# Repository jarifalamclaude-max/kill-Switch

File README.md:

# Magnetic Kill Switch (100 A)

Magnetic kill switch for an underwater robot on a 4S–6S LiPo. The board sits inside the hull and the magnet plug sits outside. Plug in: the ESCs get power. Pull the plug out: power is cut about 1.5 ms later.

There are two boards with the **same circuit**, both for **100 A** with **XT90 in (battery) and XT90 out (ESCs)**:

| | Through-hole | SMD (small) |
|---|---|---|
| Board | `kicad/ks_tht.kicad_pcb`, 123 × 100 mm | `kicad/ks_smd.kicad_pcb`, 80 × 75 mm |
| Parts | 108 (4 of them test pads), all through-hole | 96 (4 of them test pads): TOLL, SOIC, SOT-23, 0805; XT90s, B0512S and sensor plugs through-hole |
| Switch | 8 × IRFB3206 (TO-220) | 4 × IPT007N06N (TOLL) |
| Controller | one LM339 + isolated gate supply (B0512S) + PC817 | same circuit in SMD parts |
| 100 A path | bare copper strips with 8 AWG bare wire soldered on | same idea |
| Copper | 2 layers, 2 oz, green solder mask | same |

**Neither board has been built or tested yet.** Everything below comes from calculations, KiCad DRC (0 violations, 0 unconnected on both boards) and ngspice simulations of the netlists taken from the PCBs: [`SIMULATION_RESULT.md`](SIMULATION_RESULT.md).

Schematic (drawn from the PCB netlist): [`docs/kill_switch_tht_schematic.png`](docs/kill_switch_tht_schematic.png), [SVG](docs/kill_switch_tht_schematic.svg).

## Opening in KiCad (3D view)

Open `kicad/ks_tht.kicad_pro` (or `ks_smd.kicad_pro`) in **KiCad 7, 8, 9 or 10**. Every 3D model the boards use is in `kicad/3dmodels/` and the footprints point at it through `${KIPRJMOD}`. The 3D view shows all parts on any of those versions, even without KiCad's 3D library installed. Keep the `kicad/` folder together (the zips do). The XT90 footprints are in the project library `kicad/ks.pretty`. KiCad 6 cannot open KiCad 7 files.

## Why no reed switch in the power path

A reed switch carries well under 1 A and burns at the arc of a DC break at tens of amps. So the magnet only drives sensors. The current is switched by MOSFETs.

## How it works

1. **Two sensors in series.** A Hall module (KY-003, A3144) and a reed door contact (MC-38) must both see the magnet before anything turns on. A Hall stuck on, a welded reed, a cut cable, a Hall without power or a shorted Hall wire still kill (all simulated).
2. **Arm delay and debounce.** The sensors pull ARM high. ARM charges EN through 100 kΩ / 10 µF, so the switch starts about 0.8 s after the plug goes in. Losing ARM empties EN through a 2N3904 in about 1.5 ms. A sensor gap shorter than about 1 ms (vibration) is ignored, and a real pull kills in about 1.5 ms.
3. **Pre-charge first.** An IRF9540N charges the ESC capacitors through a 0.5 A PTC and 2 × 22 Ω (1.4 A at 4S, 2.1 A at 6S). Without it a few hundred amps would rush into cold capacitors.
4. **One LM339 does the sequencing.**
   - EN above 2.5 V starts the pre-charge.
   - If VOUT does not keep up with a ramp that rises with VIN (a shorted ESC bus), the pre-charge stops and stays off until the magnet is pulled.
   - The main MOSFETs close only when VOUT is above half of VIN.
   - The same comparator trips when a short pulls VOUT down while running.
5. **Main switch.** 8 × IRFB3206 in parallel (through-hole board) as a high-side switch.
   - The gate supply is an isolated 5 V → 12 V module (B0512S) whose output floats on the MOSFET sources, so the gates get about 12.8 V on any pack.
   - A PC817 connects it to the gates through a diode and 10 kΩ. A 220 nF capacitor (with 100 Ω) makes VOUT ramp up gently: 19 A peak when the MOSFETs close.
   - When the opto lets go, a BC327 pulls the gates down fast (R37 = 47 kΩ lets it pull them all the way below 1.5 V).
6. **Clamps.** 1.5KE33A TVS on the battery and ESC sides, P6KE18A between gate and source, 15 V zener on the gate supply.
7. **LEDs.** Blue HALL and blue REED (each sensor sees the magnet) and red LIVE (ESCs powered).

Not included (to keep it simple): under- and over-voltage lockout, a second independent kill path, an over-current trip below a hard short, and a status line to the Jetson. **Put a 125–150 A fuse (ANL / MIDI / MEGA) in the battery + lead.** The board kills a hard short in about 0.5 ms; an overload below that is the fuse's job.

## Numbers (through-hole board, simulated)

| | Value |
|---|---|
| MOSFET drop, 8 in parallel | 25 mV at 60 A, 42 mV at 100 A |
| Board copper at 100 A, with the 8 AWG wires | 2.5 W (without the wires: 9.3 W) |
| MOSFETs at 100 A, with the wires | 4.2 W in total (25 °C max Rds(on)), 11–15 A each |
| Gate voltage | 12.8 V on 4S and 6S |
| Kill time after the magnet leaves | 1.5 ms (4S and 6S), also with any one sensor fault; 14 mJ in the MOSFETs |
| Ignored sensor gap | 0.8 ms tested (vibration) |
| Short on the ESC side while live | off in 0.43 / 0.44 ms (4S / 6S); 1.0 J / 2.3 J shared by the 8 MOSFETs; gate peak 15.7 / 16.0 V; battery side peak 26.6 / 36.3 V |
| Magnet in with the ESC side shorted | never turns on; 0.29 J in the pre-charge resistors |
| Battery spike when killing 100 A | 19.5 V peak on 4S, 27.9 V on 6S |
| SMD board (4 × IPT007N06N) | 18 mV at 100 A, gate 13.3 V, kill 1.6 ms, short off in 0.45 / 0.48 ms; with the 8 AWG wires: copper 1.8 W, MOSFETs 22–29 A each (without: 8.3 W, Q1 47 A) |

All 15 scenarios for each board, the weakest optocoupler, and the copper current solve: [`SIMULATION_RESULT.md`](SIMULATION_RESULT.md). Magnet field, sensor placement and plug retention: [`calc/report.md`](calc/report.md).

## 100 A: the bare strips and 8 AWG wire

PCB copper alone cannot carry 100 A: the 2 oz copper would lose 9 W, and the MOSFET nearest the XT90s would take 29 A of the 100. So every 100 A path has a **bare copper strip** (no solder mask). Solder **8 AWG bare copper wire** (3.3 mm solid, or bare earthing wire) along each strip:

- **VOUT** (top, above the MOSFET pins): from the J2 + pin along the whole strip.
- **VIN** (top, below the MOSFETs, under their tabs): from the J1 + pin along the whole strip.
- **GND** (bottom): bend the wire into a C on the bare strip, from the J2 − pin to the J1 − pin.

With the wires the copper loses 2.5 W at 100 A and the 8 MOSFETs share the current within 11–15 A each. The SMD board needs the same wires (VIN above the MOSFETs, VOUT below them and down to J2 +, GND underneath between the XT90 minus pins): with them its 4 MOSFETs carry 22–29 A each, without them Q1 takes 47 A. The through-hole MOSFET tabs are all VIN. A flat copper or aluminium bar bolted across all 8 tabs (M3, no insulators needed) is optional; it spreads the heat so that Q1 runs as cool as the others.

## XT90

- J1 = **XT90PW-M** (male, right-angle PCB) for the battery's XT90; J2 = **XT90PW-F** (female) for the ESC harness. Both face out of the left edge.
- An XT90 is rated **45 A continuous, 90 A burst**. Short 100 A bursts (all thrusters at full throttle for seconds) are normal XT90 use; 100 A for minutes heats each XT90 by several watts. For long 100 A runs use two XT90s per side, or AS150 / XT150 (different footprint).
- Use 8 AWG silicone cable from the battery and to the ESCs, as short as possible.

## Buying

Full lists with quantities: [`kicad/bom_tht_grouped.csv`](kicad/bom_tht_grouped.csv) (through-hole) and [`kicad/bom_smd_grouped.csv`](kicad/bom_smd_grouped.csv) (SMD). Main parts of the through-hole board:

- 8 × IRFB3206PbF (TO-220), 1 × IRF9540NPbF.
- AMASS XT90PW-M and XT90PW-F (right-angle PCB mount).
- Mornsun B0512S-1WR3 (5 V → 12 V isolated, SIP-4). Check its pin order against the board: 1 GND, 2 Vin, 3 0 V, 4 +Vo.
- LM339N (DIP-14), PC817 (DIP-4), L7805CV. A K7805-500R3 or R-78E5.0-0.5 switching module fits the 7805's holes and runs cooler on 6S.
- 2 × 1.5KE33A, P6KE18A, 1N4744A, 1N4007, 2 × 1N4148, BZX55C12.
- Littelfuse RXEF050 PTC, 2 × 22 Ω 2 W.
- About 0.35 m of 8 AWG bare copper wire, and a 125–150 A fuse for the battery lead.
- KY-003 Hall module. Check its pin order (S, +, −) with a multimeter: some clones swap + and −.
- MC-38 wired door contact, sold in Bangladesh ([ElectronicsBD](https://electronics.com.bd/components-price-in-Bangladesh/mc-38-wired-door-window-sensor-magnetic-switch-home-alarm-system), [BDTronics](https://www.bdtronics.com/mc38-magnetic-switch.html)). Listings disagree on "normally open" and "normally closed", so check with a multimeter: it must close when the magnet is near.
- N52 magnet, 15 mm diameter × 10 mm, axially magnetised.

**Ordering the PCB (JLCPCB):** upload `kill_switch_tht_gerber_jlcpcb.zip` (or `kill_switch_smd_gerber_jlcpcb.zip`). Set 2 layers, 1.6 mm, **2 oz outer copper**, green solder mask (the default), HASL.

## Wiring

- Battery → 125–150 A fuse → J1 (XT90, battery). ESC harness → J2 (XT90, ESCs). The ground passes through the board from J2 − to J1 − along the bottom GND wire.
- J3 → KY-003 (1 = S, 2 = +, 3 = −). J4 → MC-38 (2 wires, either way round).
- Run the battery + and − as a twisted pair, at least 10 cm from the sensors.
- There is no reverse-polarity protection on the power path. The XT90 is keyed, so keep it that way.

## Mechanics (side mount)

- The dock is glued to the outside of the hull (no holes through the hull). The hull wall must be non-magnetic: acrylic, polycarbonate or aluminium, not steel.
- The plug carries the magnet with its **south pole toward the hull**: the A3144 only reacts to a south pole on its printed face. If the HALL LED stays off with the plug in, flip the magnet.
- An O-ring on the plug snaps into a groove in the dock. Pulling it out takes 10–20 N, against 0.29 N of plug weight, 1.4 N at 5 g of vibration and 1.2 N of water drag at 1.5 m/s. A slot along the dock bore lets water in and out, so there is no suction and no trapped water.
- Inside, a printed bracket holds the A3144 flat against the wall on the plug's axis (9.5 mm from the magnet, about 104 mT, 3× margin) and the MC-38 12 mm off the axis. How to fit it, step by step: [`mount/`](mount/) (video with voice-over).
- Keep steel away from the sensors. Park the pulled plug at least 120 mm away (30 cm is better), never on a steel part.

## Pre-dive check

1. Plug out, battery in: all three LEDs off.
2. Push the plug in: both blue LEDs (HALL, REED) on, then about 1 s later the red LIVE LED on. If only one blue LED lights, do not dive.
3. Pull the plug: LIVE off at once, the thrusters stop.
4. Pull the plug with a luggage scale once: it should need 10–20 N.

## Check before trusting it

- Build one board and test it on a bench supply with a current limit first, then with the battery and one ESC, then at full current. After a long full-throttle run, feel the MOSFETs, the wires and the XT90s.
- Measure the KY-003 and MC-38 with the magnet: KY-003 modules use A3144 or clones, and reed sensitivity varies by maker.
- The B0512S output is unregulated (about 14 V at light load in the model); the 15 V zener and the P6KE18A keep the gate below 20 V.
- The simulation models (MOSFETs fitted to datasheet numbers, behavioural comparators, opto, isolated module) are approximations.

## Folders

| Folder / file | Contents |
|---|---|
| `kicad/build_tht.py`, `route_tht.py` | Through-hole board: parts, netlist and placement; routing (0/45-degree corners), pours, bare strips, BRACU Duburi logo and name, DRC |
| `kicad/build_smd.py`, `route_smd.py` | SMD board, same circuit |
| `kicad/ks_tht.*`, `ks_smd.*`, `drc_*.rpt`, `bom_*.csv` | KiCad boards, DRC reports, BOMs and order lists |
| `kicad/3dmodels/`, `ks.pretty/`, `fp-lib-table` | 3D models of every part (found through `${KIPRJMOD}`), XT90 footprints |
| `kicad/bundle_3d.py`, `make_xt90.py`, `make_outputs.py`, `gridroute.py` | 3D-model bundling and green stackup, XT90 footprints and models, gerbers/zips/pictures, the router |
| `kicad/simulation/` | `run_tht.py --board tht/smd` (15 scenarios from the PCB netlist), `copper_tht.py` (copper current solve), `make_result.py` |
| `gerber_tht/`, `gerber_smd/`, `kill_switch_*_gerber_jlcpcb.zip`, `kill_switch_*_kicad.zip` | Gerbers for JLCPCB and the KiCad projects (with 3D models) |
| `veroboard/` | Perfboard version of the through-hole board, with schematic, wire list and parts |
| `pcb-3d/` | 3D through-hole board with every part and the current paths on the real copper |
| `3d/` | Tutorial: video `kill_switch_tutorial.mp4` (86 s, English voice-over, 100 A board) and an interactive 3D scene of a diver pulling and re-arming the plug; `make_voice.py` + `narration/` make the voice, `render_video.js` renders and mixes it |
| `mech/` | Dock, plug, T-handle and inside sensor bracket (OpenSCAD, STL) |
| `mount/` | Sensor mounting guide: video `sensor_mounting.mp4` (72 s, English voice-over) and a 3D scene of where the Hall (KY-003) and reed (MC-38) go inside the hull and how to fit them |
| `kicad/build_ks.py`, `route_ks.py`, `ks_power.*`, `gerber/`, `kill_switch_gerber_jlcpcb.zip`, `kill_switch_kicad.zip` | First SMD version (LM5060, M5 lugs, 118 × 120 mm), kept for reference |
| `calc/` | `design_calc.py`: magnet field, reed placement, cable stray field, timing, plug retention (`report.md`) |

## Rebuilding

With KiCad 7 and its Python (`KICAD7_FOOTPRINT_DIR` and `KICAD7_SYMBOL_DIR` set to the KiCad libraries):

```bash
cd kicad && python3 build_tht.py && python3 route_tht.py && python3 make_bom.py bom_tht.csv bom_tht_grouped.csv && python3 make_outputs.py tht
```

```bash
cd kicad/simulation && python3 run_tht.py --board tht && python3 summary_tht.py --board tht && python3 copper_tht.py --board tht --wires && python3 make_result.py
```

The SMD board is the same with `build_smd.py`, `route_smd.py`, `make_outputs.py smd` and `--board smd`.

## Bangla-English summary

- Duita board, ekoi circuit, duitai 100 A: through-hole (8 ta IRFB3206, 123 × 100 mm) ar choto SMD (4 ta IPT007N06N, 80 × 75 mm).
- Battery ar ESC dui dikei XT90. XT90 45 A continuous / 90 A burst rated: thruster-er short burst thik ache; onek khon 100 A cholle 2 ta XT90 parallel ba AS150 din.
- 100 A-er jonno bare strip gulote 8 AWG khali tama-r tar solder korte hobe (VIN, VOUT upore; GND niche C shape). Tar chara copper-e 9 W gorom hoy, tar dile 2.5 W.
- Hall (KY-003) ar reed (MC-38) dutoi magnet dekhle tobei chalu hoy. Magnet tanle ~1.5 ms-e power off; chalu obosthay short hole 0.4 ms-e off; short thakle chalu-i hoy na.
- KiCad 7, 8, 9, 10 — jekono version-e khulle 3D view-te sob part dekha jabe (3D model project-er bhitorei ache). Board green.
- Battery + tare 125–150 A fuse rakho. Board ekhono banano/test kora hoyni: prothome bench supply-te current limit diye test korben.

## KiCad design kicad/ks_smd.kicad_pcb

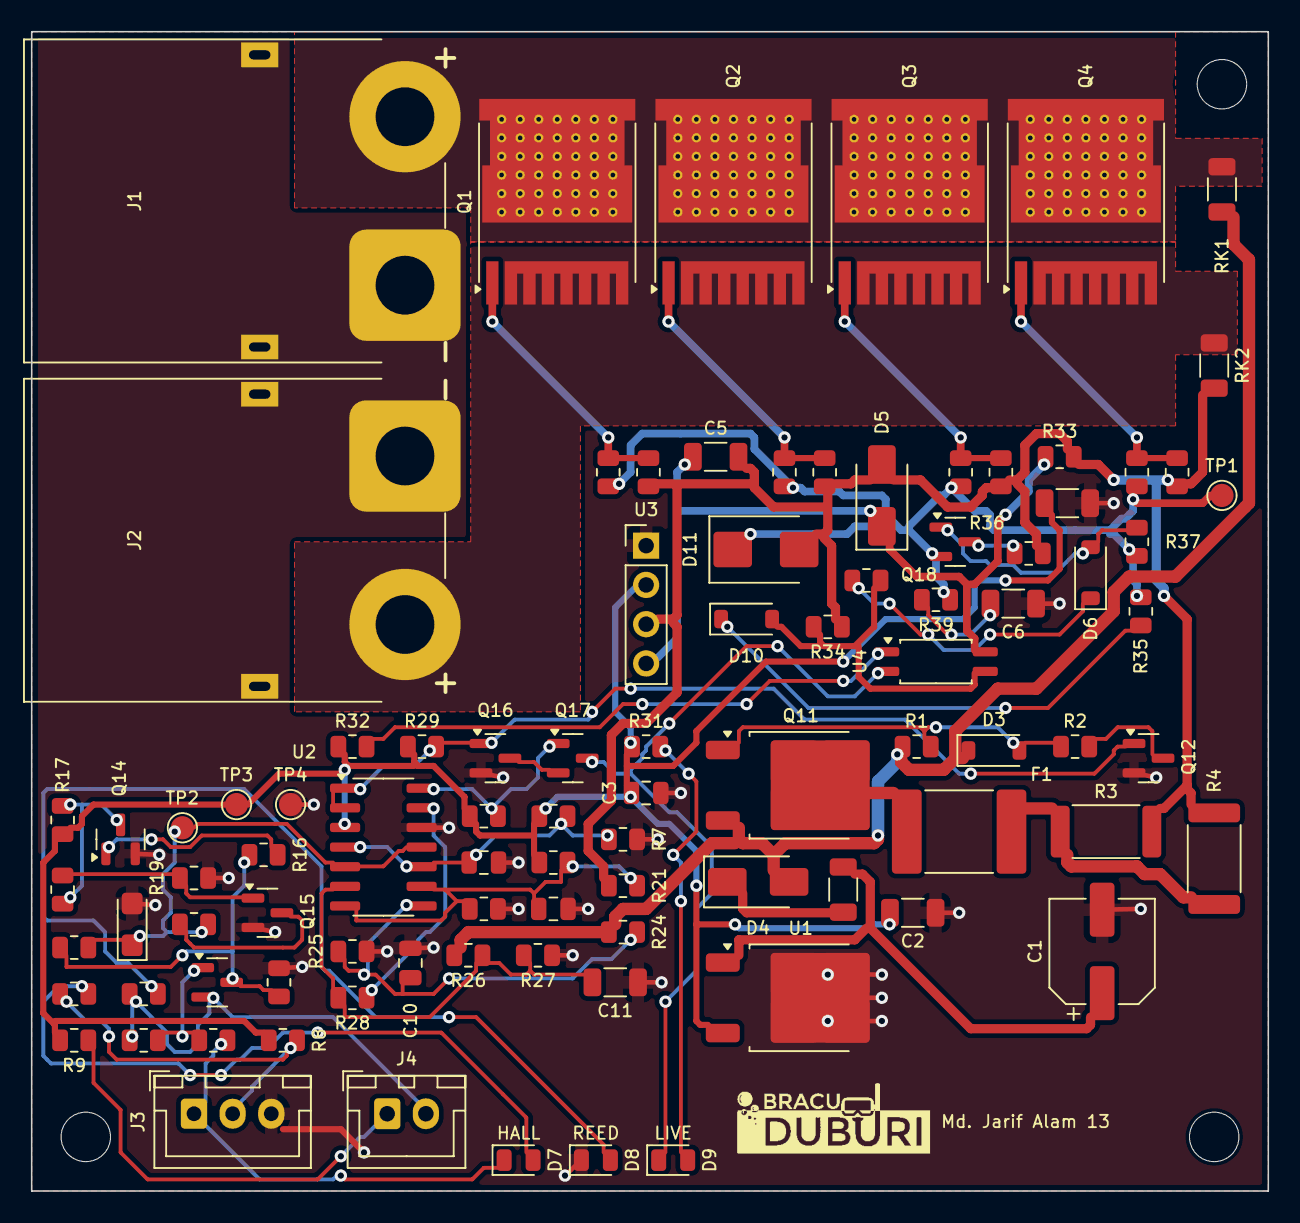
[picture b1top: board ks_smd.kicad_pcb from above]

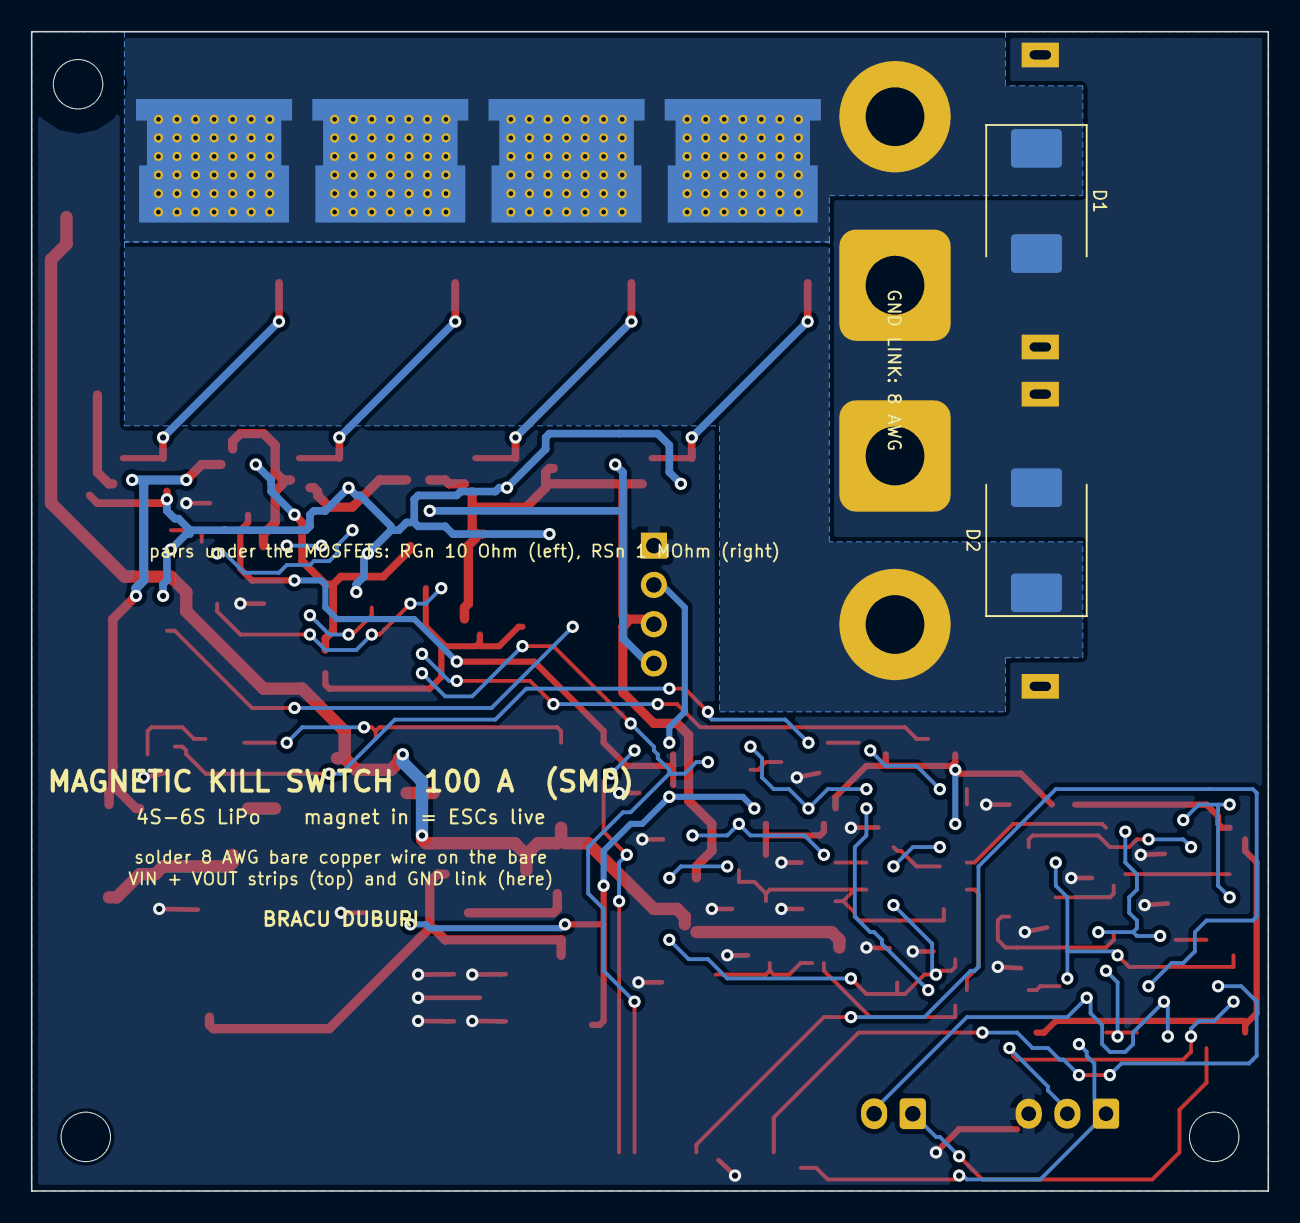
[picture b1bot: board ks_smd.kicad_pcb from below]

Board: 2 copper layers, 80.0 x 75.0 mm, 99 parts (2 on the bottom side), 48 nets.

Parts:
C1: 47u 50V; CP_Elec_6.3x7.7
C2, C4: 10u 25V; C_1206_3216Metric
C3, C8: 100n; C_0805_2012Metric
C5: 22u 25V; C_1206_3216Metric
C6: 220n 100V X7R; C_1206_3216Metric
C7: 10u 16V tantalum; CP_EIA-3216-18_Kemet-A
C9, C10: 10n; C_0805_2012Metric
C11: 3.3u X7R 50V; C_1206_3216Metric
D1, D2: SMCJ28A; D_SMC
D3: BZT52C12; D_SOD-123
D4: S1M; D_SMA
D5: SMAZ15; D_SMA
D6, D10: 1N4148W; D_SOD-123
D7: blue HALL; LED_0805_2012Metric
D8: blue REED; LED_0805_2012Metric
D9: red LIVE; LED_0805_2012Metric
D11: SMBJ15A; D_SMB
F1: MF-SM050/60-2 (0.5 A, 60 V); Fuse_2920_7451Metric
H1, H2, H3: M3 nylon; MountingHole_3.2mm_M3
J1: XT90PW-M battery IN; AMASS_XT90PW-M_1x02_P10.90mm_Horizontal
J2: XT90PW-F ESC OUT; AMASS_XT90PW-F_1x02_P10.90mm_Horizontal
J3: HALL MODULE (KY-003: S + -); JST_XH_B3B-XH-A_1x03_P2.50mm_Vertical
J4: REED (MC-38); JST_XH_B2B-XH-A_1x02_P2.50mm_Vertical
Q1, Q2, Q3, Q4: IPT007N06N; Infineon_PG-HSOF-8-1_ThermalVias
Q11: FQD11P06; TO-252-2
Q12, Q16, Q17: 2N7002; SOT-23
Q13: MMBT3906; SOT-23
Q14, Q15: MMBT3904; SOT-23
Q18: BC807-40; SOT-23
R1, R11, R37: 47k; R_0805_2012Metric
R2, R34: 22k; R_0805_2012Metric
R3, R4: 22 2512; R_2512_6332Metric
R5: 10; R_1206_3216Metric
R6, R7, R10, R16, R17, R18, R29, R30, R35: 10k; R_0805_2012Metric
R8, R9, R39: 100; R_0805_2012Metric
R12, R33: 4.7k; R_0805_2012Metric
R13, R14, R28, R31, R38: 1k; R_0805_2012Metric
R15, R19: 100k; R_0805_2012Metric
R20: 220; R_0805_2012Metric
R21: 75k 1%; R_0805_2012Metric
R22, R25: 10k 1%; R_0805_2012Metric
R23: 470k; R_0805_2012Metric
R24: 160k 1%; R_0805_2012Metric
R26: 1M; R_0805_2012Metric
R27: 68k; R_0805_2012Metric
R32: 330; R_0805_2012Metric
R36: 47; R_0805_2012Metric
RG1, RG2, RG3, RG4: 10; R_0805_2012Metric
RK1, RK2: 0R; R_1206_3216Metric
RS1, RS2, RS3, RS4: 1M; R_0805_2012Metric
TP1: FG; TestPoint_Pad_D1.5mm
TP2: EN; TestPoint_Pad_D1.5mm
TP3: V5; TestPoint_Pad_D1.5mm
TP4: GND; TestPoint_Pad_D1.5mm
U1: L7805CDT; TO-252-2
U2: LM339D; SOIC-14_3.9x8.7mm_P1.27mm
U3: B0512S-1WR3; PinHeader_1x04_P2.54mm_Vertical
U4: EL357N; SOP-4_4.4x2.6mm_P1.27mm

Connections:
ARM: Q13.3, R12.1, R15.1, R16.1
CATH: D9.1, Q17.3, U4.2
DONE: Q17.1, R30.2, U2.14
DRV: D10.2, R34.1, R38.2, U4.3
DRVD: D10.1, R35.1
EN: C7.1, R15.2, R20.2, TP2.1, U2.5, U2.11
FG: D11.1, Q18.2, R35.2, R37.1, R39.2, RG1.2, RG2.2, RG3.2, RG4.2, TP1.1
FGC: C6.1, R39.1
G1: Q1.1, RG1.1, RS1.1
G2: Q2.1, RG2.1, RS2.1
G3: Q3.1, RG3.1, RS3.1
G4: Q4.1, RG4.1, RS4.1
GND: C1.2, C2.2, C3.2, C4.2, C6.2, C7.2, C8.2, C9.2, C10.2, C11.2, D1.2, D2.2, D8.1, J1.1, J1.MP, J2.1, J2.MP, J3.3, Q12.2, Q14.2, Q15.2, Q16.2, R7.2, R12.2, R19.2, R22.2, R25.2, R27.2, TP4.1, U1.2, U2.12, U3.1
HALL: D7.1, J3.1, R10.2
HLA: D7.2, R13.2
LVA: D9.2, R31.2
NARM: Q14.3, R17.2, R18.1
PCD: F1.1, Q11.2
PCDN: Q12.3, R2.2
PCEN: Q12.1, Q16.1, R29.2, U2.1, U2.2
PCF: F1.2, R3.1, R4.1
PCG: D3.2, Q11.1, R1.2, R2.1
QAB: Q13.1, R10.1, R11.2
QDB: Q15.1, R18.2, R19.1
QDC: Q15.3, R20.1
QGM: Q16.3, Q17.2
QIB: Q14.1, R16.2
QOB: D6.2, Q18.1, R37.2
QOC: Q18.3, R36.1
QOD: D6.1, R38.1
RAMP: C11.1, R26.2, R27.1, R28.1, U2.6
REF: C8.1, R6.2, R7.1, U2.4, U2.10
RIN: J4.1, R9.2
RLA: D8.2, R14.2
ROUT: J4.2, Q13.2, R11.1, R14.1
RRST: R28.2, U2.13
SRC: C5.2, D5.2, D11.2, R3.2, R4.2, R21.1, R33.2, R34.2, R36.2, RK2.2, RS1.2, RS2.2, RS3.2, RS4.2, U3.3
UGA: R32.2, U4.1
V5: C2.1, C3.1, C4.1, R6.1, R8.1, R9.1, R17.1, R23.1, R29.1, R30.1, R31.1, R32.1, TP3.1, U1.3, U2.3, U3.2
V5S: J3.2, R8.2, R13.1
V12F: C5.1, D5.1, R33.1, U3.4, U4.4
VIN: D1.1, J1.2, Q1.3, Q2.3, Q3.3, Q4.3, RK1.1
VIND: C10.1, R24.2, R25.1, U2.8
VIN_K: D3.1, D4.2, Q11.3, R1.1, R24.1, R26.1, RK1.2
VOD: C9.1, R21.2, R22.1, R23.2, U2.7, U2.9
VOUT: D2.1, J2.2, Q1.2, Q2.2, Q3.2, Q4.2, RK2.1
VR1: D4.1, R5.1
VR2: C1.1, R5.2, U1.1

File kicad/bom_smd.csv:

ref,value,footprint
C1,"47u 50V",CP_Elec_6.3x7.7
C2,"10u 25V",C_1206_3216Metric
C3,"100n",C_0805_2012Metric
C4,"10u 25V",C_1206_3216Metric
C5,"22u 25V",C_1206_3216Metric
C6,"220n 100V X7R",C_1206_3216Metric
C7,"10u 16V tantalum",CP_EIA-3216-18_Kemet-A
C8,"100n",C_0805_2012Metric
C9,"10n",C_0805_2012Metric
C10,"10n",C_0805_2012Metric
C11,"3.3u X7R 50V",C_1206_3216Metric
D1,"SMCJ28A",D_SMC
D2,"SMCJ28A",D_SMC
D3,"BZT52C12",D_SOD-123
D4,"S1M",D_SMA
D5,"SMAZ15",D_SMA
D6,"1N4148W",D_SOD-123
D7,"blue HALL",LED_0805_2012Metric
D8,"blue REED",LED_0805_2012Metric
D9,"red LIVE",LED_0805_2012Metric
D10,"1N4148W",D_SOD-123
D11,"SMBJ15A",D_SMB
F1,"MF-SM050/60-2 (0.5 A, 60 V)",Fuse_2920_7451Metric
J1,"XT90PW-M battery IN",AMASS_XT90PW-M_1x02_P10.90mm_Horizontal
J2,"XT90PW-F ESC OUT",AMASS_XT90PW-F_1x02_P10.90mm_Horizontal
J3,"HALL MODULE (KY-003: S + -)",JST_XH_B3B-XH-A_1x03_P2.50mm_Vertical
J4,"REED (MC-38)",JST_XH_B2B-XH-A_1x02_P2.50mm_Vertical
Q1,"IPT007N06N",Infineon_PG-HSOF-8-1_ThermalVias
Q2,"IPT007N06N",Infineon_PG-HSOF-8-1_ThermalVias
Q3,"IPT007N06N",Infineon_PG-HSOF-8-1_ThermalVias
Q4,"IPT007N06N",Infineon_PG-HSOF-8-1_ThermalVias
Q11,"FQD11P06",TO-252-2
Q12,"2N7002",SOT-23
Q13,"MMBT3906",SOT-23
Q14,"MMBT3904",SOT-23
Q15,"MMBT3904",SOT-23
Q16,"2N7002",SOT-23
Q17,"2N7002",SOT-23
Q18,"BC807-40",SOT-23
R1,"47k",R_0805_2012Metric
R2,"22k",R_0805_2012Metric
R3,"22 2512",R_2512_6332Metric
R4,"22 2512",R_2512_6332Metric
R5,"10",R_1206_3216Metric
R6,"10k",R_0805_2012Metric
R7,"10k",R_0805_2012Metric
R8,"100",R_0805_2012Metric
R9,"100",R_0805_2012Metric
R10,"10k",R_0805_2012Metric
R11,"47k",R_0805_2012Metric
R12,"4.7k",R_0805_2012Metric
R13,"1k",R_0805_2012Metric
R14,"1k",R_0805_2012Metric
R15,"100k",R_0805_2012Metric
R16,"10k",R_0805_2012Metric
R17,"10k",R_0805_2012Metric
R18,"10k",R_0805_2012Metric
R19,"100k",R_0805_2012Metric
R20,"220",R_0805_2012Metric
R21,"75k 1%",R_0805_2012Metric
R22,"10k 1%",R_0805_2012Metric
R23,"470k",R_0805_2012Metric
R24,"160k 1%",R_0805_2012Metric
R25,"10k 1%",R_0805_2012Metric
R26,"1M",R_0805_2012Metric
R27,"68k",R_0805_2012Metric
R28,"1k",R_0805_2012Metric
R29,"10k",R_0805_2012Metric
R30,"10k",R_0805_2012Metric
R31,"1k",R_0805_2012Metric
R32,"330",R_0805_2012Metric
R33,"4.7k",R_0805_2012Metric
R34,"22k",R_0805_2012Metric
R35,"10k",R_0805_2012Metric
R36,"47",R_0805_2012Metric
R37,"47k",R_0805_2012Metric
R38,"1k",R_0805_2012Metric
R39,"100",R_0805_2012Metric
RG1,"10",R_0805_2012Metric
RG2,"10",R_0805_2012Metric
RG3,"10",R_0805_2012Metric
RG4,"10",R_0805_2012Metric
RK1,"0R",R_1206_3216Metric
RK2,"0R",R_1206_3216Metric
RS1,"1M",R_0805_2012Metric
RS2,"1M",R_0805_2012Metric
RS3,"1M",R_0805_2012Metric
RS4,"1M",R_0805_2012Metric
TP1,"FG",TestPoint_Pad_D1.5mm
TP2,"EN",TestPoint_Pad_D1.5mm
TP3,"V5",TestPoint_Pad_D1.5mm
TP4,"GND",TestPoint_Pad_D1.5mm
U1,"L7805CDT",TO-252-2
U2,"LM339D",SOIC-14_3.9x8.7mm_P1.27mm
U3,"B0512S-1WR3",PinHeader_1x04_P2.54mm_Vertical
U4,"EL357N",SOP-4_4.4x2.6mm_P1.27mm

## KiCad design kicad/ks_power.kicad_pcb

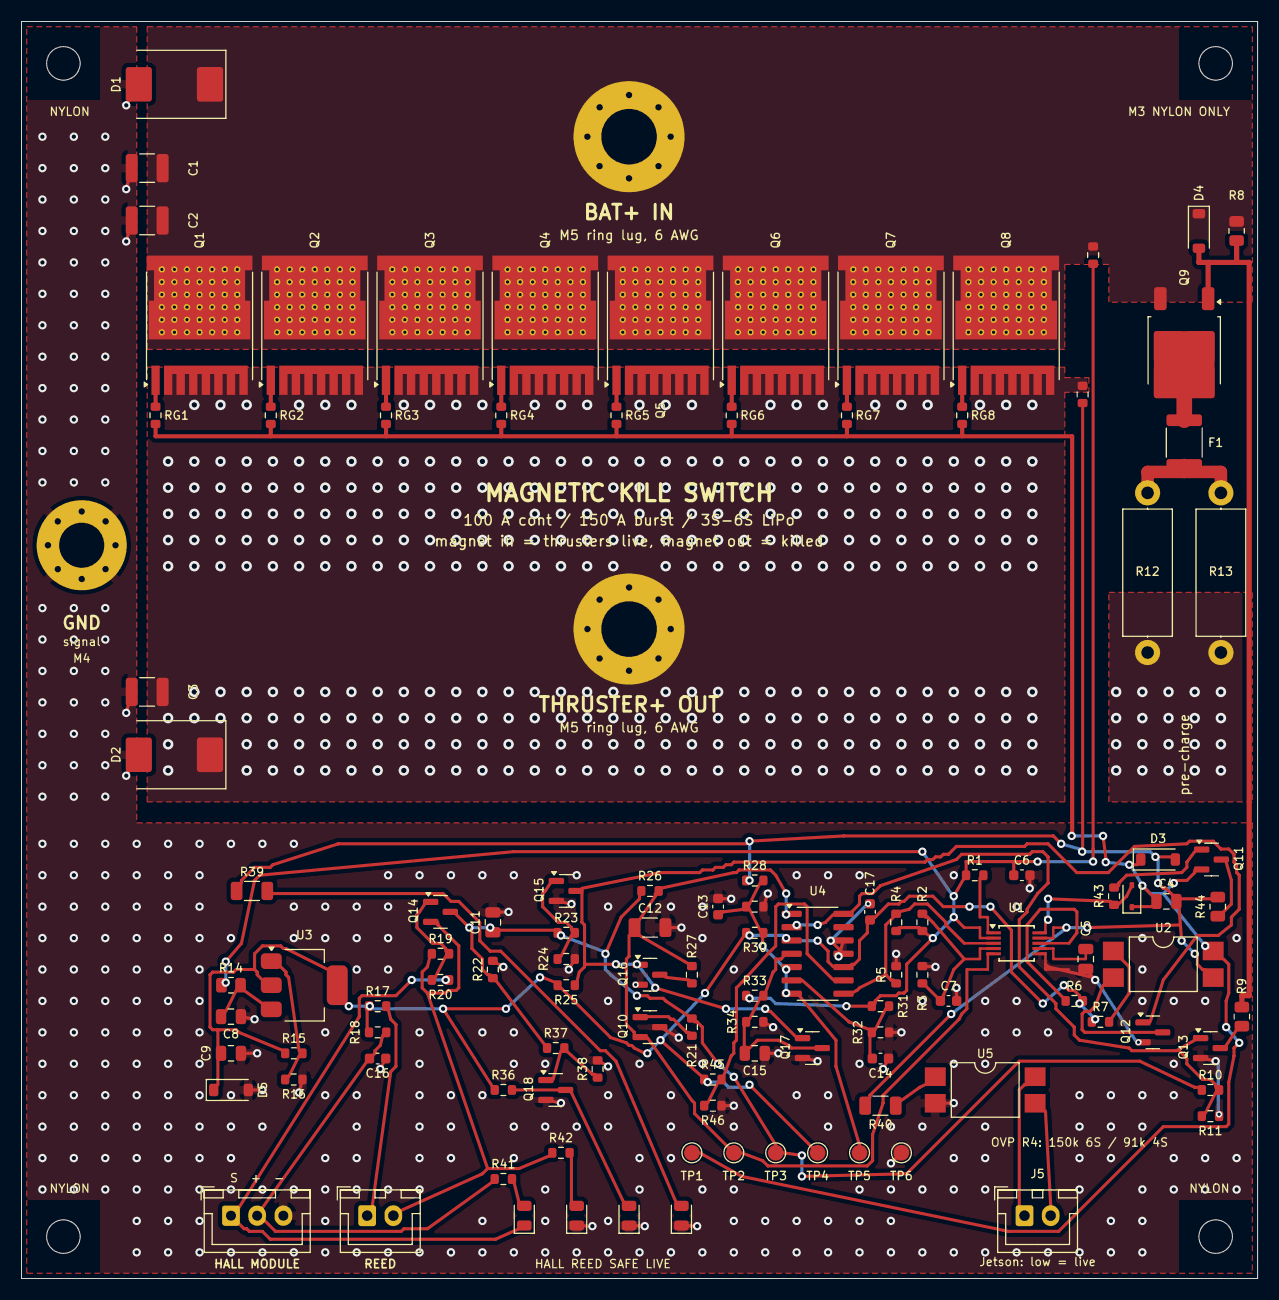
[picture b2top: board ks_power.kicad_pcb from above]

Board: 2 copper layers, 118.0 x 120.0 mm, 121 parts (0 on the bottom side), 55 nets.

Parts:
C1, C2, C3: 2.2u 100V; C_1210_3225Metric
C4: 47n 50V; C_0805_2012Metric
C5: 470n; C_0805_2012Metric
C6: 100n 100V; C_0603_1608Metric
C7, C13, C14: 10n; C_0603_1608Metric
C8: 1u 50V; C_0805_2012Metric
C9: 10u 16V; C_0805_2012Metric
C11: 2.2u; C_0805_2012Metric
C12: 22u 16V; C_1206_3216Metric
C15: 3.3u; C_0805_2012Metric
C16, C17: 100n; C_0603_1608Metric
D1: SMDJ26A; D_SMC
D2: SMCJ26A; D_SMC
D3: BZT52C15; D_SOD-123
D4: BZT52C12; D_SOD-123
D5: BZT52C6V2; D_SOD-123
D6: blue HALL; LED_0805_2012Metric
D7: blue REED; LED_0805_2012Metric
D8: green SAFE; LED_0805_2012Metric
D9: BAT54WS; D_SOD-323
F1: PTC 0.5A 30V 1812; Fuse_1812_4532Metric
H1, H2, H3, H4: M3 nylon; MountingHole_3.2mm_M3
J1: BAT+ IN (M5); MountingHole_5.3mm_M5_Pad_Via
J2: THRUSTER+ OUT (M5); MountingHole_5.3mm_M5_Pad_Via
J3: GND (M4); MountingHole_4.3mm_M4_Pad_Via
J4: HALL MODULE (KY-003: S + -); JST_XH_B3B-XH-A_1x03_P2.50mm_Vertical
J5: STATUS to Jetson; JST_XH_B2B-XH-A_1x02_P2.50mm_Vertical
J6: REED CONTACT (MC-38); JST_XH_B2B-XH-A_1x02_P2.50mm_Vertical
LED1: red LIVE; LED_0805_2012Metric
Q1, Q2, Q3, Q4, Q5, Q6, Q7, Q8: IPT007N06N; Infineon_PG-HSOF-8-1_ThermalVias
Q9: FQD11P06; TO-252-2
Q10, Q11: MMBT3906; SOT-23
Q12, Q13, Q15, Q16, Q17, Q18: 2N7002; SOT-23
Q14: BSS84; SOT-23
R1: 4.32k 1%; R_0603_1608Metric
R2, R34: 47k; R_0603_1608Metric
R3, R5, R20, R23, R37: 10k; R_0603_1608Metric
R4: 150k; R_0603_1608Metric
R6, R10, R19, R24, R25, R26, R38: 100k; R_0603_1608Metric
R7, R36, R41, R42, R43: 1k; R_0603_1608Metric
R8: 47k; R_0805_2012Metric
R9: 22k; R_0805_2012Metric
R11, R30, R33: 1M; R_0603_1608Metric
R12, R13: 22 2W; R_Axial_DIN0414_L11.9mm_D4.5mm_P15.24mm_Horizontal
R14: 10; R_0805_2012Metric
R15: 240 1%; R_0603_1608Metric
R16: 750 1%; R_0603_1608Metric
R17, R18: 100; R_0603_1608Metric
R21: 4.7k; R_0603_1608Metric
R22: 2.2k; R_0603_1608Metric
R27: 10; R_0603_1608Metric
R28: 90.9k 1%; R_0603_1608Metric
R29, R32, R46: 10k 1%; R_0603_1608Metric
R31: 191k 1%; R_0603_1608Metric
R39: 4.7k; R_1206_3216Metric
R40: 10k; R_1206_3216Metric
R44: 220; R_0805_2012Metric
R45: 15.8k 1%; R_0603_1608Metric
RG1, RG2, RG3, RG4, RG5, RG6, RG7, RG8: 10; R_0603_1608Metric
RK1: 0R (VIN Kelvin); R_0603_1608Metric
RK2: 0R (VOUT Kelvin); R_0603_1608Metric
TP1: FG; TestPoint_Pad_D1.5mm
TP2: EN; TestPoint_Pad_D1.5mm
TP3: ARM; TestPoint_Pad_D1.5mm
TP4: V5; TestPoint_Pad_D1.5mm
TP5: VOD; TestPoint_Pad_D1.5mm
TP6: GND; TestPoint_Pad_D1.5mm
U1: LM5060; MSOP-10_3x3mm_P0.5mm
U2: PC817 (gate kill); SMDIP-4_W9.53mm
U3: LM317; SOT-223-3_TabPin2
U4: LM339; SOIC-14_3.9x8.7mm_P1.27mm
U5: PC817 (status); SMDIP-4_W9.53mm

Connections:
ADJ: R15.2, R16.1, U3.1
ARM: C11.1, Q14.3, R10.1, R21.2, R22.1, R23.1, R26.1, R37.1, TP3.1
ARMG: Q15.1, R23.2, R24.1
EN: C12.1, Q10.2, R26.2, R27.2, TP2.1, U1.5, U4.1
END: Q16.3, R27.1
FG: C4.1, D3.1, D9.1, Q11.2, RG1.2, RG2.2, RG3.2, RG4.2, RG5.2, RG6.2, RG7.2, RG8.2, TP1.1, U2.4
G1: Q1.1, RG1.1
G2: Q2.1, RG2.1
G3: Q3.1, RG3.1
G4: Q4.1, RG4.1
G5: Q5.1, RG5.1
G6: Q6.1, RG6.1
G7: Q7.1, RG7.1
G8: Q8.1, RG8.1
GDRV: D9.2, R43.1, U1.10
GND: C1.1, C2.1, C3.1, C5.2, C6.2, C7.2, C8.2, C9.2, C11.2, C12.2, C13.2, C14.2, C15.2, C16.2, C17.2, D1.2, D2.2, D5.2, D7.1, D8.1, J3.1, J4.3, LED1.1, Q10.3, Q12.2, Q13.2, Q15.2, Q16.2, Q17.2, Q18.2, R3.2, R5.2, R11.2, R16.2, R22.2, R24.2, R29.2, R32.2, R34.2, R38.2, R46.2, TP6.1, U1.6, U4.11, U4.12, U5.2
HALL: D6.1, J4.1, R20.2
HG: Q14.1, R19.2, R20.1
HLA: D6.2, R41.2
KA: R7.2, U2.1
KC: Q12.3, U2.2
LIVEA: LED1.2, R39.2
LSAFE: D8.2, Q18.3, R36.2
NARM: Q12.1, Q15.3, Q16.1, Q17.1, R25.2
OVP: R4.2, R5.1, U1.3, U4.8
PCD: F1.1, Q9.2
PCEN: Q13.1, R10.2, R11.1, U4.2, U4.14
PCF: F1.2, R12.1, R13.1
PCG: D4.2, Q9.1, R8.2, R9.1
PDRV: Q13.3, R9.2
PGD: R6.1, U1.8
PNB: Q10.1, R21.1
PNB2: Q11.1, R43.2
QOFF: Q11.3, R44.1
RAMP: C15.1, Q17.3, R33.2, R34.1, U4.4
REF2: R45.2, R46.1, U4.9
RIN: J6.1, R17.2
RLA: D7.2, R42.2
ROUT: J6.2, Q14.2, R19.1, R42.1
SAFEG: Q18.1, R37.2, R38.1
SNS: R1.2, U1.1
STA: R40.2, U5.1
STC: J5.1, U5.4
STE: J5.2, U5.3
TMR: C5.1, U1.7
UV: C7.1, R2.2, R3.1, U1.4
V5: C9.1, C17.1, D5.1, R6.2, R7.1, R15.1, R17.1, R18.1, R25.1, R30.1, R36.1, R45.1, TP4.1, U3.2, U4.3, U4.10
V5S: C16.1, J4.2, R18.2, R41.1
VIN: C1.2, C2.2, D1.1, D4.1, J1.1, Q1.3, Q2.3, Q3.3, Q4.3, Q5.3, Q6.3, Q7.3, Q8.3, Q9.3, R8.1, RK1.1
VIND: C14.1, R31.2, R32.1, U4.6
VINL: C8.1, R14.2, U3.3
VIN_K: C6.1, R1.1, R2.1, R4.1, R14.1, R31.1, R33.1, RK1.2, U1.2
VOD: C13.1, R28.2, R29.1, R30.2, TP5.1, U4.5, U4.7
VOUT: C3.2, D2.1, J2.1, Q1.2, Q2.2, Q3.2, Q4.2, Q5.2, Q6.2, Q7.2, Q8.2, R12.2, R13.2, RK2.1
VOUT_K: C4.2, D3.2, R28.1, R39.1, R40.1, R44.2, RK2.2, U1.9, U2.3

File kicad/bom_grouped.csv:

qty,value,footprint,refs,buy
3,2.2u 100V,C_1210_3225Metric,C1 C2 C3,"1210 X7R ceramic, 100V"
1,47n 50V,C_0805_2012Metric,C4,"0805 X7R ceramic, 50V"
1,470n,C_0805_2012Metric,C5,"0805 X7R ceramic, 25 V or more"
1,100n 100V,C_0603_1608Metric,C6,"0603 X7R ceramic, 100V"
3,10n,C_0603_1608Metric,C7 C13 C14,"0603 X7R ceramic, 25 V or more"
1,1u 50V,C_0805_2012Metric,C8,"0805 X7R ceramic, 50V"
1,10u 16V,C_0805_2012Metric,C9,"0805 X7R ceramic, 16V"
1,2.2u,C_0805_2012Metric,C11,"0805 X7R ceramic, 25 V or more"
1,22u 16V,C_1206_3216Metric,C12,"1206 X7R ceramic, 16V"
1,3.3u,C_0805_2012Metric,C15,"0805 X7R ceramic, 25 V or more"
2,100n,C_0603_1608Metric,C16 C17,"0603 X7R ceramic, 25 V or more"
1,SMDJ26A,D_SMC,D1,"Littelfuse SMDJ26A (3 kW TVS, 26 V standoff, SMC)"
1,SMCJ26A,D_SMC,D2,"Littelfuse SMCJ26A (1.5 kW TVS, 26 V standoff, SMC)"
1,BZT52C15,D_SOD-123,D3,"BZT52C series zener, SOD-123"
1,BZT52C12,D_SOD-123,D4,"BZT52C series zener, SOD-123"
1,BZT52C6V2,D_SOD-123,D5,"BZT52C series zener, SOD-123"
1,blue HALL,LED_0805_2012Metric,D6,"0805 LED, blue"
1,blue REED,LED_0805_2012Metric,D7,"0805 LED, blue"
1,green SAFE,LED_0805_2012Metric,D8,"0805 LED, green"
1,BAT54WS,D_SOD-323,D9,"BAT54WS Schottky, SOD-323"
1,PTC 0.5A 30V 1812,Fuse_1812_4532Metric,F1,"1812 PTC fuse, hold 0.5 A, rated 30 V or more (60 V better for 6S) - verify the rating"
1,BAT+ IN (M5),MountingHole_5.3mm_M5_Pad_Via,J1,"M5 ring lug, 6 AWG or thicker cable, M5 brass/stainless bolt + nut"
1,THRUSTER+ OUT (M5),MountingHole_5.3mm_M5_Pad_Via,J2,"M5 ring lug, 6 AWG or thicker cable, M5 brass/stainless bolt + nut"
1,GND (M4),MountingHole_4.3mm_M4_Pad_Via,J3,"M4 ring lug, thin wire to battery minus (logic ground only)"
1,HALL MODULE (KY-003: S + -),JST_XH_B3B-XH-A_1x03_P2.50mm_Vertical,J4,JST XH 3-pin header B3B-XH-A + housing XHP-3 for the KY-003 cable
1,STATUS to Jetson,JST_XH_B2B-XH-A_1x02_P2.50mm_Vertical,J5,JST XH 2-pin header B2B-XH-A + housing XHP-2
1,REED CONTACT (MC-38),JST_XH_B2B-XH-A_1x02_P2.50mm_Vertical,J6,JST XH 2-pin header B2B-XH-A + housing XHP-2 for the MC-38 cable
1,red LIVE,LED_0805_2012Metric,LED1,"0805 LED, red"
8,IPT007N06N,Infineon_PG-HSOF-8-1_ThermalVias,Q1 Q2 Q3 Q4 Q5 Q6 Q7 Q8,"Infineon IPT007N06N (60 V, 0.75 mOhm max, TOLL)"
1,FQD11P06,TO-252-2,Q9,"onsemi FQD11P06TM (-60 V P-FET, DPAK)"
2,MMBT3906,SOT-23,Q10 Q11,"MMBT3906 PNP, SOT-23"
6,2N7002,SOT-23,Q12 Q13 Q15 Q16 Q17 Q18,"2N7002 N-FET, SOT-23"
1,BSS84,SOT-23,Q14,"BSS84 P-FET, SOT-23"
1,4.32k 1%,R_0603_1608Metric,R1,0603 resistor 1%
2,47k,R_0603_1608Metric,R2 R34,0603 resistor 1% or 5%
5,10k,R_0603_1608Metric,R3 R5 R20 R23 R37,0603 resistor 1% or 5%
1,150k,R_0603_1608Metric,R4,0603 resistor 1% or 5%
7,100k,R_0603_1608Metric,R6 R10 R19 R24 R25 R26 R38,0603 resistor 1% or 5%
5,1k,R_0603_1608Metric,R7 R36 R41 R42 R43,0603 resistor 1% or 5%
1,47k,R_0805_2012Metric,R8,0805 resistor 1% or 5%
1,22k,R_0805_2012Metric,R9,0805 resistor 1% or 5%
3,1M,R_0603_1608Metric,R11 R30 R33,0603 resistor 1% or 5%
2,22 2W,R_Axial_DIN0414_L11.9mm_D4.5mm_P15.24mm_Horizontal,R12 R13,"22 Ohm 2 W metal oxide or metal film, axial (pulse 1.5 J each)"
1,10,R_0805_2012Metric,R14,0805 resistor 1% or 5%
1,240 1%,R_0603_1608Metric,R15,0603 resistor 1%
1,750 1%,R_0603_1608Metric,R16,0603 resistor 1%
2,100,R_0603_1608Metric,R17 R18,0603 resistor 1% or 5%
1,4.7k,R_0603_1608Metric,R21,0603 resistor 1% or 5%
1,2.2k,R_0603_1608Metric,R22,0603 resistor 1% or 5%
9,10,R_0603_1608Metric,R27 RG1 RG2 RG3 RG4 RG5 RG6 RG7 RG8,0603 resistor 1% or 5%
1,90.9k 1%,R_0603_1608Metric,R28,0603 resistor 1%
3,10k 1%,R_0603_1608Metric,R29 R32 R46,0603 resistor 1%
1,191k 1%,R_0603_1608Metric,R31,0603 resistor 1%
1,4.7k,R_1206_3216Metric,R39,1206 resistor 1% or 5%
1,10k,R_1206_3216Metric,R40,1206 resistor 1% or 5%
1,220,R_0805_2012Metric,R44,0805 resistor 1% or 5%
1,15.8k 1%,R_0603_1608Metric,R45,0603 resistor 1%
1,0R (VIN Kelvin),R_0603_1608Metric,RK1,"0603 resistor 1% or 5%, 0 Ohm jumper"
1,0R (VOUT Kelvin),R_0603_1608Metric,RK2,"0603 resistor 1% or 5%, 0 Ohm jumper"
1,LM5060,MSOP-10_3x3mm_P0.5mm,U1,TI LM5060MM/NOPB (VSSOP-10)
1,PC817 (gate kill),SMDIP-4_W9.53mm,U2,"Sharp/Everlight PC817 SMD (SMDIP-4, gull wing)"
1,LM317,SOT-223-3_TabPin2,U3,LM317 in SOT-223 (e.g. LM317DCYR)
1,LM339,SOIC-14_3.9x8.7mm_P1.27mm,U4,LM339DR or LM339ADR (SOIC-14)
1,PC817 (status),SMDIP-4_W9.53mm,U5,"Sharp/Everlight PC817 SMD (SMDIP-4, gull wing)"

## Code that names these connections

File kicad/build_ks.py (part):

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  - Arm chain, energise to arm: 5 V -> reed (closed by the magnet) -> P-MOSFET switched by the Hall sensor -> ARM.
    Loss of either sensor, the cable, the 5 V or the magnet pulls ARM low and kills.
  - Second, independent kill path: an optocoupler shorts the MOSFET gates to source whenever ARM is low.
Sensors are bought modules that plug in: a 3-pin Hall module (KY-003 style, A3144, output low with the magnet)
  on J4 and a 2-wire reed door contact (MC-38 style, closed with the magnet) on J6. Both sit on the inside of the
  hull wall behind the magnet; both must see the magnet for the thrusters to get power.

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    pl("Q11", *SOT23, 113.6, L + 3.0, 0, "MMBT3906", {"1": "PNB2", "2": "FG", "3": "QOFF"})
    pl("R44", *R08, 114.2, L + 7.5, 90, "220", {"1": "QOFF", "2": "VOUT_K"})
    pl("C4", *C08, 109.3, L + 7.0, 0, "47n 50V", {"1": "FG", "2": "VOUT_K"})
    pl("U2", *OPTO, 109.0, L + 13.0, 0, "PC817 (gate kill)", {"1": "KA", "2": "KC", "3": "VOUT_K", "4": "FG"}, ref_at=(109.0, L + 9.6))
    pl("R7", *R06, 103.0, L + 18.5, 0, "1k", {"1": "V5", "2": "KA"})
    pl("Q12", *SOT23, 108.0, L + 19.5, 0, "2N7002", {"1": "NARM", "2": "GND", "3": "KC"})
    # pre-charge driver
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    # logic 5 V: LM317 from the VIN Kelvin line
    pl("R14", *R08, 20.0, L + 15.0, 0, "10", {"1": "VIN_K", "2": "VINL"})
    pl("C8", *C08, 20.0, L + 18.0, 0, "1u 50V", {"1": "VINL", "2": "GND"})
    pl("U3", "Package_TO_SOT_SMD", "SOT-223-3_TabPin2", 27.0, L + 15.0, 0, "LM317", {"1": "ADJ", "2": "V5", "3": "VINL"}, ref_at=(27.0, L + 10.2))
    pl("R15", *R06, 26.0, L + 21.5, 0, "240 1%", {"1": "V5", "2": "ADJ"})
    pl("R16", *R06, 26.0, L + 24.0, 0, "750 1%", {"1": "ADJ", "2": "GND"})
    pl("C9", *C08, 20.0, L + 21.5, 0, "10u 16V", {"1": "V5", "2": "GND"})
    pl("D5", *SOD123, 20.0, L + 25.0, 0, "BZT52C6V2", {"1": "V5", "2": "GND"})
    # status to the Jetson through an optocoupler
    pl("U5", *OPTO, 92.0, L + 25.0, 0, "PC817 (status)", {"1": "STA", "2": "GND", "3": "STE", "4": "STC"}, ref_at=(92.0, L + 21.6))
    pl("R40", *R12, 82.0, L + 26.5, 0, "10k", {"1": "VOUT_K", "2": "STA"})
    pl("J5", "Connector_JST", "JST_XH_B2B-XH-A_1x02_P2.50mm_Vertical", 95.75, L + 37.0, 0, "STATUS to Jetson", {"1": "STC", "2": "STE"}, ref_at=(97.0, L + 33.0))
    # bought sensors: a 3-pin Hall module (KY-003 style, S + -) and a 2-wire reed door contact (MC-38 style)
    pl("J4", "Connector_JST", "JST_XH_B3B-XH-A_1x03_P2.50mm_Vertical", 20.0, L + 37.0, 0, "HALL MODULE (KY-003: S + -)",
       {"1": "HALL", "2": "V5S", "3": "GND"}, hide_ref=True)
    pl("J6", "Connector_JST", "JST_XH_B2B-XH-A_1x02_P2.50mm_Vertical", 33.0, L + 37.0, 0, "REED CONTACT (MC-38)",
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
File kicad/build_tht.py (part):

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part("Q17", "TO92", "2N7000", {"1": "QGM", "2": "DONE", "3": "CATH"})
part("D9", "LED", "red LIVE", two("CATH", "LVA"))
part("R31", "R", "1k", two("V5", "LVA"))
part("U4", "DIP4", "PC817", {"1": "UGA", "2": "CATH", "3": "DRV", "4": "V12F"})
part("R32", "R", "330", two("V5", "UGA"))
# floating gate drive (ground = VOUT)
part("U3", "SIP4", "B0512S-1WR3", {"1": "GND", "2": "V5", "3": "SRC", "4": "V12F"})
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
